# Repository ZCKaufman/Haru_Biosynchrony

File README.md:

# Haru_Biosynchrony
The Haru Biosynchrony detection device is a pair of devices created by Cameron Middleton, Carmen Hernandez, Dawson Thompson, Jonathan Ott, and Zachary Kaufman at Indiana University for the Intelligent Systems Engineering Senior Capstone (ENGR-E490/E491) course. The device is designed to be used with the Haru social desktop robot prototype by Honda Research Institute, and was created as a tool for the R-House Human-Robot Interaction lab to use for their studies involving intergenerational synchrony during interactions with Haru. 

Contents:
- Hardware Specifications
- Assembly Instructions
- Demo Instructions
- Using the Device
- Running the Code
- Understanding the Output

## Hardware Specifications

## Assembly Instructions

## Demo Instructions

## Using the Device
- This system uses two devices and finds relative bio-synchrony between them. Ensuring that both devices are currently placed on the participants is important for quality metrics of synchrony. 
1. Place the compute module on the top of your non-dominant wrist and secure with velcro strap firmly but not uncomfortably
2. Place the PPG sensor (the one with purple and red wires) on your index finger by slipping your index finger inside the black sleeve so that the red sensor is on the padding at the bottom of your finger
3. Place the PPG sensor (the one with the two thin wires) on your middle and forefinger by slipping those fingers into the black sleeves so that the metal sensors are on the bottom of the center of your finger
4. Place your non-dominant hand (the one with the sensors on it) at your waist if standing, or on your lap if sitting
    - Note: It is best for sensor resolution if the sensors are not moved a lot during the activity, try encouraging participants to keep their non-dominant hand at this position and to use their dominant hand for the activity
5. Now plug in the compute module to the Haru Zotac computer through a USB port and follow the `Running the Code` instructions

## Running the Code
- System Requirements
    - Python 3.10+
    - Ubuntu 20.04
    - ROS Noetic
- Instructions
    1. Open the Arduino IDE in two separate windows
    2. Open a terminal window and run the command `roscore`
    3. In the first window open the file `A_ROS_Arduino.ino` and in the second window open the file `B_ROS_Arduino.ino`
    4. In both windows make sure that the selected board (under Tools) is "Arduino Micro" and the selected port is the port that the Arduino is plugged into
    5. Click the blue/green "Upload" button in the upper left corner of the screen in both windows
    6. Now open two new tabs/windows in terminal and type in the following command for both devices: 'rosrun rosserial_arduino serial_node.py __name:="DevA" _port:=/dev/ttyACM0`
        NOTE: There are two underscores before `name` and one before `port`
        NOTE: Your port may be different, use the one found in the Arduino window for the device you are using under "Tools"
        - Run the same command again but rename the second device to `DevB` and change the port to whatever port the second device is plugged into
    7. Open the Haru_Biosynchrony repository in VSCode 
    8. Open a terminal within VSCode and run the following command `pyenv activate haru_sync`, this will activate the Haru Synchrony Python environment. This environment is installed on the Zotac machines from Honda
    9. Now run the code by entering the following command `python Robot_Code/synchrony.py`
    10. The code should now be running. Every 5 seconds a synchrony metric will be published to ROS and printed into the VS Code terminal
    11. To stop and start over, just click ctrl+c and rerun the command from step 9 (ix)

## Understanding the output
The output from this program will be a metric of synchrony called a Pearson Correlation and it will update the metric every 5 seconds. There will be a score published for heart rate and GSR separately. The metric will be published on ROS as well as printed to the terminal running the program. 
- Negative Score (-1 to 0)
    - A negative score means that the subjects are experiencing negative synchrony, meaning that their heart rate or GSR has an inverse correlation. An inverse correlation means that the subjects' heart rate or GSR data is trending in opposite values from each other. A score of less than -0.5 represents a strong inverse correlation.
- Zero Score (0)
    - A 0 score means that the two participants are neither in sync nor moving out of sync. Their heart rate and GSR data is not correlated.
- Positive Score (0 to 1)
    - A positive score means that the subjects are experiencing synchrony, meaning that their heart rate or GSR has a direct correlation. A score of greater than 0.5 represents a strong correlation.

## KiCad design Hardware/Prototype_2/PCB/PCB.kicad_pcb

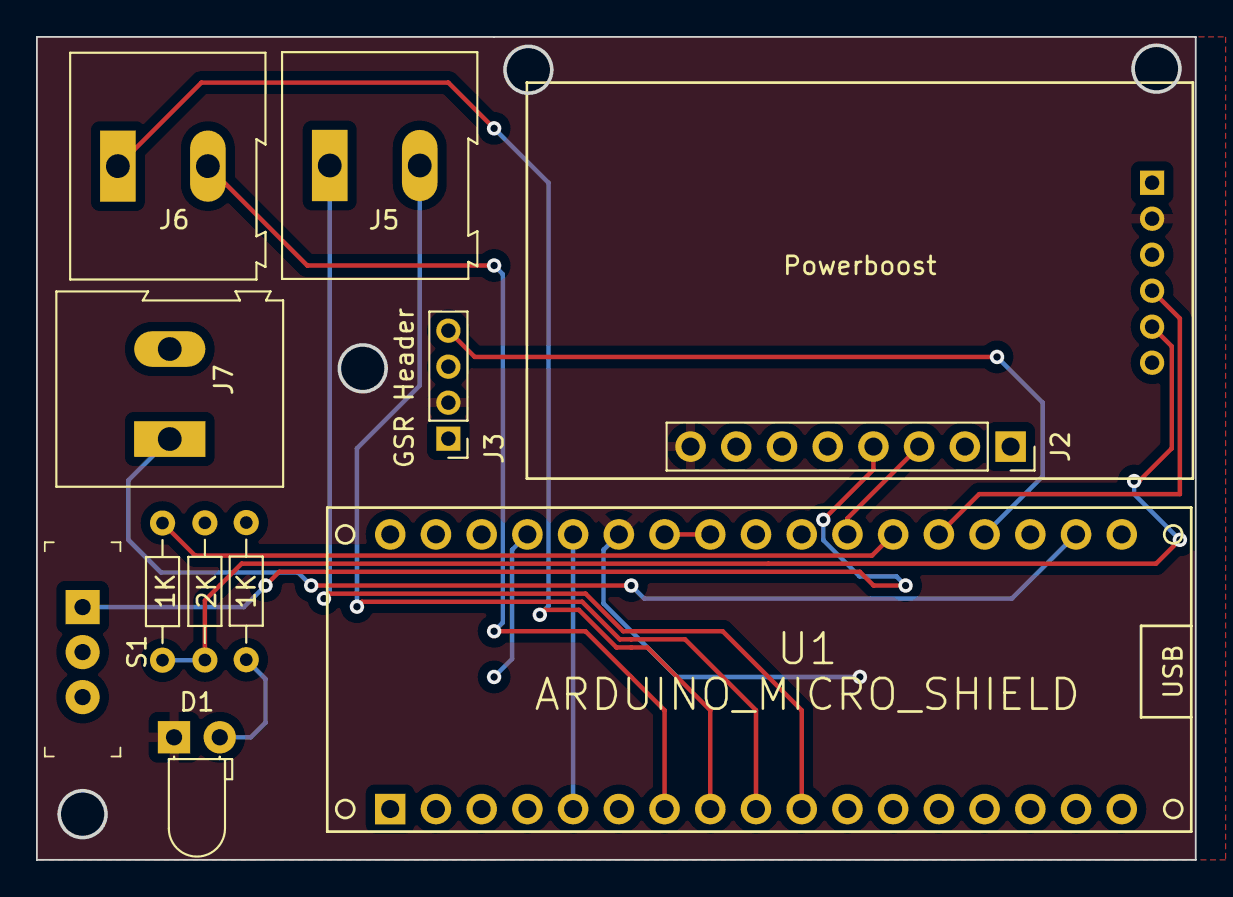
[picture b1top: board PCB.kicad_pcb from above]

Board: 2 copper layers, 64.3 x 45.6 mm, 12 parts (1 on the bottom side), 14 nets.

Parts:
D1: LED; LED_D3.0mm_Horizontal_O1.27mm_Z6.0mm
J1: Bluetooth Interface; PinHeader_1x06_P2.00mm_Horizontal
J2: Powerboost; PinSocket_1x08_P2.54mm_Vertical
J3: GSR Header; PinHeader_1x04_P2.00mm_Vertical
J5, J6, J7: Screw_Terminal_01x02; TerminalBlock_Altech_AK300-2_P5.00mm
R1: 2K; R_Axial_DIN0204_L3.6mm_D1.6mm_P7.62mm_Horizontal
R2, R3: 1K; R_Axial_DIN0204_L3.6mm_D1.6mm_P7.62mm_Horizontal
S1: EG1218; Switch_Slide_11.6x4mm_EG1218
U1: ARDUINO_MICRO_SHIELD

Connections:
+3V3: J7.1, U1.3.3V
+5V: D1.1 (K), J1.2, J2.8, J3.2, U1.5V (+5V)
/PowerBoost_EN: J2.4, S1.1
GND: J1.3, J2.2, J2.5, J2.7, J3.1, J7.2, R1.1, R3.1, S1.2, U1.GND
unnamed: D1.2 (A), R3.2
unnamed: J1.4, U1.A1
unnamed: J1.5, R1.2, R2.2
unnamed: J2.3, U1.A3
unnamed: J3.4, U1.A0
unnamed: J5.1, U1.5 (5(PWM))
unnamed: J5.2, U1.4 (4/A6)
unnamed: J6.1, U1.3 (3(PWM)/SCL)
unnamed: J6.2, U1.2 (2/SDA)
unnamed: R2.1, U1.A2

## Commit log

2023-01-17 Create Basic Output
2023-01-18 Added Demo Code for PPG Sensor, First Version of Arduino Firmware
2023-01-18 Updated Firmware, Created Serial2CSV Python Tool
2023-01-19 Started PCB for Prototype V2
2023-01-24 Added CAD Files for Prototype 1
2023-01-24 Reformatted Prototype 2 Directory Structure
2023-02-10 Added ROS publishers for body data, known bug: body.rValue requires conversion from float to string before publishing. Code currently fails.
2023-02-14 PCB Shape Finalized
2023-02-14 Added PCB STEP file
2023-02-28 PPG stuff
2023-02-28 PCB Final Version, Added Gerber Files
2023-03-07 Added ROS publishers to Arduino Firmware
2023-03-20 Added rospy functionality
2023-04-12 Cleaned repo
2023-04-18 Added ROS integrated Arduino code to robot code folder
2023-04-18 added second user; still uses .csv
2023-04-20 Added modified serial2CSV
2023-04-20 gets synchrony from csv
2023-04-23 treats csv as 200 data points; improved synchrony
2023-04-24 Added ROS functionality to synchrony code and created A and B device Arduino code
2023-04-24 Added code to make our Arduino code Micro compatible
2023-04-24 Strings
2023-04-24 Finalized syncrony functionality for two devices
2023-04-25 Pearson correlation synchrony
2023-04-25 Updated robot synchrony code for new correlation metric
2023-04-25 Added some Prototype 2 hardware files
2023-04-27 Removed duplicate files
2023-04-27 modified Understanding the output section
2023-04-27 modified final section
2023-04-27 Fixed threading issue
